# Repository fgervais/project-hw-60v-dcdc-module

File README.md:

# 4.3V to 60V input / 0.8V to 30V output switching converter

- [PCB v1.0.0-5-g07f53f4](#pcb-v100-5-g07f53f4)
  - [Switching converter analysis](#switching-converter-analysis)
    - [Switch node](#switch-node)
  - [Output (5V, 2x 10uF 50V output capacitors)](#output-5v-2x-10uf-50v-output-capacitors)
  - [Output (5V, 2x 22uF 16V output capacitors)](#output-5V-2x-22uF-16V-output-capacitors)
- [PCB v1.0.0-5-g07f53f4 (hack1)](#pcb-v100-5-g07f53f4-hack1)
  - [Switching converter analysis](#switching-converter-analysis-lmr51625)
  - [Output (5V, 2x 22uF 16V output capacitors)](#output-5V-lmr51625-2x-22uF-16V-output-capacitors)
- [PCB v2.0.0](#pcb-v200)
  - [Switching converter analysis](#switching-converter-analysis-v200)
  - [Output (5V, Snubber 5.1Ω/100pF)](#output-5v-v200-snubber-51ω100pf)
  - [Output (5V, Snubber 5.1Ω/100pF, 3.3uF)](#output-5v-v200-snubber-51ω100pf-33uf)

## PCB v1.0.0-5-g07f53f4

### Switching converter analysis

50 ohms series termination at the SW node.

#### Switch node

| Input Voltage | Waveform | Rising edge |
|---------------|----------|-------------|
| 10V           |  |  |
| 20V           |  |  |
| 48V           |  |  |

### Output (5V, 2x 10uF 50V output capacitors)

| Input Voltage | No Load | 50 mA | 500 mA | 1 A |
|---------------|---------|-------|--------|-----|
| 10V           |  |  |  |  |
| 20V           |  |  |  |  |
| 48V           |  |  |  |  |

| Input Voltage | No Load | 50 mA | 500 mA | 1 A |
|---------------|---------|-------|--------|-----|
| 10V           |  |  |  |  |
| 20V           |  |  |  |  |
| 48V           |  |  |  |  |

#### Noise

| Input Voltage | No Load | 50 mA | 500 mA | 1 A |
|---------------|---------|-------|--------|-----|
| 10V           | 73.60 mV (1.47%) | 73.60 mV (1.47%) | 20.80 mV (0.42%) | 19.20 mV (0.38%) |
| 20V           | 49.20 mV (0.98%) | 49.20 mV (0.98%) | 26.00 mV (0.52%) | 27.20 mV (0.54%) |
| 48V           | 49.20 mV (0.98%) | 49.20 mV (0.98%) | 45.20 mV (0.90%) | 40.40 mV (0.81%) |

### Output (5V, 2x 22uF 16V output capacitors)

| Input Voltage | No Load | 50 mA | 500 mA | 1 A |
|---------------|---------|-------|--------|-----|
| 10V           |  |  |  |  |
| 20V           |  |  |  |  |
| 48V           |  |  |  |  |

| Input Voltage | No Load | 50 mA | 500 mA | 1 A |
|---------------|---------|-------|--------|-----|
| 10V           |  |  |  |  |
| 20V           |  |  |  |  |
| 48V           |  |  |  |  |

#### Noise

| Input Voltage | No Load | 50 mA | 500 mA | 1 A |
|---------------|---------|-------|--------|-----|
| 10V           | 31.40 mV (0.63%) | 32.40 mV (0.65%) | 16.40 mV (0.33%) | 15.20 mV (0.30%) |
| 20V           | 22.80 mV (0.46%) | 24.40 mV (0.49%) | 19.60 mV (0.39%) | 19.20 mV (0.38%) |
| 48V           | 23.60 mV (0.47%) | 26.20 mV (0.52%) | 21.00 mV (0.42%) | 21.20 mV (0.42%) |

### Output (24V, 2x 10uF 50V output capacitors)

| Input Voltage | No Load | 50 mA | 500 mA | 1 A |
|---------------|---------|-------|--------|-----|
| 10V           |  |  |  |  |
| 20V           |  |  |  |  |
| 48V           |  |  |  |  |

| Input Voltage | No Load | 50 mA | 500 mA | 1 A |
|---------------|---------|-------|--------|-----|
| 10V           |  |  |  |  |
| 20V           |  |  |  |  |
| 48V           |  |  |  |  |

#### Noise

| Input Voltage | No Load | 50 mA | 500 mA | 1 A |
|---------------|---------|-------|--------|-----|
| 10V           |  mV (%) |  mV (%) |  mV (%) |  mV (%) |
| 20V           |  mV (%) |  mV (%) |  mV (%) |  mV (%) |
| 48V           |  mV (%) |  mV (%) |  mV (%) |  mV (%) |

## PCB v1.0.0-5-g07f53f4 (hack1)

### Switching converter analysis (LMR51625)

#### Switch node

| Input Voltage | Waveform | Rising edge |
|---------------|----------|-------------|
| 10V           |  |  |
| 20V           |  |  |
| 48V           |  |  |

### Output (5V, LMR51625, 2x 22uF 16V output capacitors)

| Input Voltage | No Load | 50 mA | 500 mA | 1 A |
|---------------|---------|-------|--------|-----|
| 10V           |  |  |  |  |
| 20V           |  |  |  |  |
| 48V           |  |  |  |  |

| Input Voltage | No Load | 50 mA | 500 mA | 1 A |
|---------------|---------|-------|--------|-----|
| 10V           |  |  |  |  |
| 20V           |  |  |  |  |
| 48V           |  |  |  |  |

#### Noise

| Input Voltage | No Load | 50 mA | 500 mA | 1 A |
|---------------|---------|-------|--------|-----|
| 10V           | 18.80 mV (0.37%) | 20.00 mV (0.40%) | 11.80 mV (0.24%) | 12.00 mV (0.24%) |
| 20V           | 13.80 mV (0.28%) | 15.40 mV (0.31%) | 15.40 mV (0.31%) | 15.20 mV (0.30%) |
| 48V           | 15.40 mV (0.31%) | 17.40 mV (0.35%) | 35.60 mV (0.71%) | 19.00 mV (0.38%) |

## PCB v2.0.0

### Switching converter analysis v2.0.0

#### Switch node

| Input Voltage | Waveform | Rising edge |
|---------------|----------|-------------|
| 10V           |  |  |
| 20V           |  |  |
| 48V           |  |  |

#### Switch node (Snubber 5.1Ω/100pF)

| Input Voltage | Rising edge |
|---------------|-------------|
| 10V           |  |
| 20V           |  |
| 48V           |  |

### Output (5V, v2.0.0, Snubber 5.1Ω/100pF)

| Input Voltage | No Load | 50 mA | 500 mA | 1 A |
|---------------|---------|-------|--------|-----|
| 10V           |  |  |  |  |
| 20V           |  |  |  |  |
| 48V           |  |  |  |  |

| Input Voltage | No Load | 50 mA | 500 mA | 1 A |
|---------------|---------|-------|--------|-----|
| 10V           |  |  |  |  |
| 20V           |  |  |  |  |
| 48V           |  |  |  |  |

### Output (5V, v2.0.0, Snubber 5.1Ω/100pF, 3.3uF)

| Input Voltage | No Load | 50 mA | 500 mA | 1 A |
|---------------|---------|-------|--------|-----|
| 10V           |  |  |  |  |
| 20V           |  |  |  |  |
| 48V           |  |  |  |  |

| Input Voltage | No Load | 50 mA | 500 mA | 1 A |
|---------------|---------|-------|--------|-----|
| 10V           |  |  |  |  |

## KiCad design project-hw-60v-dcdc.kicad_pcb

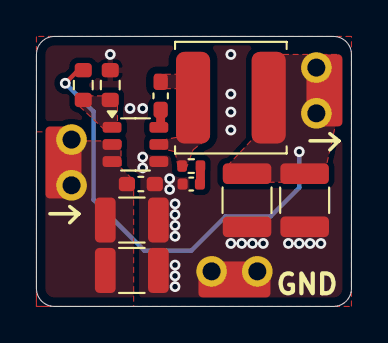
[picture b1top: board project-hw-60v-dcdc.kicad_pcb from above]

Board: 4 copper layers, 17.5 x 15.0 mm, 15 parts (0 on the bottom side), 7 nets.

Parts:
C1, C2: 10uF 100V; C_1210_3225Metric_Tight
C3: 1uF 100V; C_0603_1608Metric_Tight
C4: 0.1uF; C_0603_1608Metric_Tight
C5, C6: 10uF 50V; C_1210_3225Metric
C7: Csnub; C_0402_1005Metric
J1, J2, J3: Conn_01x01_Socket; EdgePad_1x1_Short
L1: 6.8uH; L_TDK_VLS6045EX_VLS6045AF
R2: Vchoice; R_0603_1608Metric
R3: 10k; R_0603_1608Metric
R4: Rsnub; R_0402_1005Metric
U1: LMR516x5; TSOT-23-6_Tight

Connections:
/LMR516x5 Converter/FB: R2.2, R3.1, U1.1 (FB)
/LMR516x5 Converter/Vin: C1.1, C2.1, C3.1, J1.1, U1.2 (EN), U1.3 (VIN)
/LMR516x5 Converter/Vout: C5.1, C6.1, J3.1, L1.2, R2.1
GND: C1.2, C2.2, C3.2, C5.2, C6.2, C7.2, J2.1, R3.2, U1.4 (GND)
unnamed: C7.1, R4.2
unnamed: C4.1, U1.6 (CB)
unnamed: C4.2, L1.1, R4.1, U1.5 (SW)

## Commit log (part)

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2026-01-02 sch: add 2 blocks
2026-01-02 sch: first draft
2026-01-03 pcb: first placement
2026-01-03 pcb: first routing no errors
2026-01-03 pcb: add ground vias
2026-01-03 pcb: set board edge closer to golden pads
2026-01-03 pcb: add version
2026-01-03 pcb: change tolerances to 0.25 mm
2026-01-03 pcb: update pcb version
2026-01-03 Close kicad
2026-01-04 pcb: make board 1 mm larger on the right
2026-01-04 pcb: update version
2026-01-04 Add gerbers
2026-01-08 Change entry 0.1uF cap to 1uF 100V
2026-01-08 Add assembly file
2026-02-10 Add switch node analysis to README
2026-02-20 Add output to README
2026-03-07 Update README with version hack1
2026-03-09 First placement
2026-03-10 First routing
2026-03-11 Add inner ground planes
2026-03-11 Pass DRC
2026-03-11 Add copper pour under the inductor
2026-03-12 Change ground silkscreen
2026-03-12 README: add v1 5V probe setup
2026-03-12 README: add hack1 sw node closeup
2026-03-13 README: add output probing
2026-03-16 README: Add hack1 output noise
2026-03-16 README: add hack1 noise calculation
2026-03-16 README: add output probe setup image
2026-03-21 Resize copper
2026-03-21 pcb: update silkscreen version
2026-03-21 Update gerbers
2026-04-05 Update assembly file
2026-04-19 README: add v2.0.0 switch node
2026-04-20 README: add switch node image
2026-04-27 README: add snubber 5.1ohms/100pF
2026-04-29 RAEDME: add output for Snubber 5.1Ω/100pF
2026-04-29 README: add snubber 5.1Ω/100pF output noise
2026-04-29 README: add output probe setup
